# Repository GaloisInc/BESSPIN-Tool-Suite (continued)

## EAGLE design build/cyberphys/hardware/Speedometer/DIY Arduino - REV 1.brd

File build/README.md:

# Builds for FETT #

This directory should include the instructions and codes needed to build the OSs and the apps for the bug bounty.

Initially, the builds will be leveraging [Besspin Tool-Suite](https://gitlab-ext.galois.com/ssith/tool-suite).

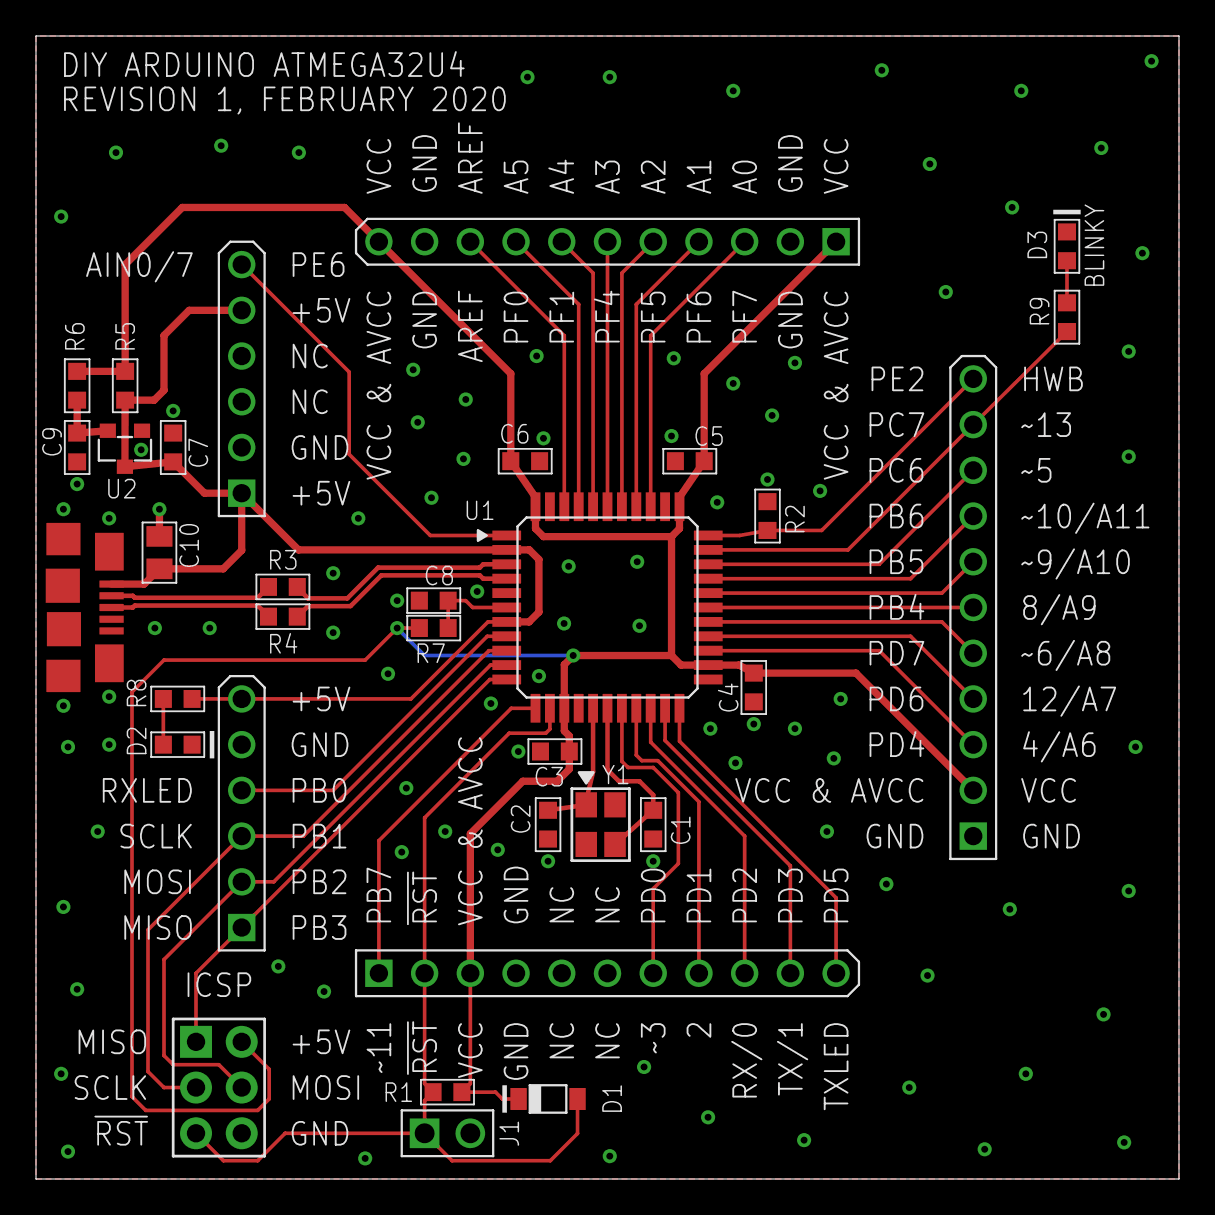
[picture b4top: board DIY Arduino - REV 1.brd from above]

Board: 2 copper layers, 63.5 x 63.5 mm, 33 parts (0 on the bottom side), 41 nets.

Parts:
C1, C2: 18p; EIA0603
C3, C4, C5, C6: 0.1u; EIA0603
C7, C8, C9: 1u; EIA0603
C10: 10u; EIA0805
CN1: 2X3M; 2X3_100MIL_ICSP
CN2: 10118192-0002LF; AMPHENOL_10118192-0002LF
CN3, CN4: 1X6_100MIL_THRU
CN5, CN6, CN7: 1X11_100MIL_THRU
D1: 1N4148WTR; SOD-123
D2: GREEN; EIA0603_LED
D3: RED; EIA0603_LED
J1: 1X2_100MIL_THRU
R1, R2: 10k; EIA0603
R3, R4: 22; EIA0603
R5: 0; EIA0603
R6, R7: DNS; EIA0603
R8, R9: 1k; EIA0603
U1: ATMEGA32U4-AUR; TQFP-44
U2: AP2125N-3.3; SOT23-3
Y1: 16 MHz; EPSON_FA-238

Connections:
!RST: CN1.5, CN5.2, D1.A, J1.1, R1.P$1, U1.13
+3V3: C9.P$2, R6.P$1, U2.2
AREF: CN7.9, U1.42
D_N: R3.P$2, U1.3
D_P: R4.P$2, U1.4
GND: C1.P$1, C2.P$1, C3.P$1, C4.P$1, C5.P$1, C6.P$1, C7.P$1, C8.P$1, C9.P$1, C10.P$1, CN1.6, CN2.5, CN2.TAB1, CN2.TAB2, CN2.TAB3, CN2.TAB4, CN2.TAB5, CN2.TAB6, CN3.2, CN4.5, CN5.4, CN5.5, CN5.6, CN6.1, CN7.2, CN7.10, D2.C, D3.C, J1.2, R2.P$1, U1.5, U1.15, U1.23, U1.35, U1.43, U2.1, Y1.2, Y1.4
unnamed: C2.P$2, U1.16, Y1.1
unnamed: D3.A, R9.P$1
unnamed: C8.P$2, R7.P$1, U1.6
unnamed: C1.P$2, U1.17, Y1.3
unnamed: D2.A, R8.P$1
PB0: CN4.4, U1.8
PB1: CN1.3, CN4.3, U1.9
PB2: CN1.4, CN4.2, U1.10
PB3: CN1.1, CN4.1, U1.11
PB4: CN6.6, U1.28
PB5: CN6.7, U1.29
PB6: CN6.8, U1.30
PB7: CN5.1, U1.12
PC6: CN6.9, U1.31
PC7: CN6.10, R9.P$2, U1.32
PD0: CN5.7, U1.18
PD1: CN5.8, U1.19
PD2: CN5.9, U1.20
PD3: CN5.10, U1.21
PD4: CN6.3, U1.25
PD5: CN5.11, U1.22
PD6: CN6.4, U1.26
PD7: CN6.5, U1.27
PE2: CN6.11, R2.P$2, U1.33
PE6: CN3.6, U1.1
PF0: CN7.8, U1.41
PF1: CN7.7, U1.40
PF4: CN7.6, U1.39
PF5: CN7.5, U1.38
PF6: CN7.4, U1.37
PF7: CN7.3, U1.36
USB_+5V: C7.P$2, C10.P$2, CN2.1, CN3.1, CN3.5, CN4.6, R5.P$2, R8.P$2, U1.2, U1.7, U2.3
USB_D_N: CN2.2, R3.P$1
USB_D_P: CN2.3, R4.P$1
VCC_&_AVCC: C3.P$2, C4.P$2, C5.P$2, C6.P$2, CN1.2, CN5.3, CN6.2, CN7.1, CN7.11, D1.C, R1.P$2, R5.P$1, R6.P$2, R7.P$2, U1.14, U1.24, U1.34, U1.44

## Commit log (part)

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2021-06-22 Fixed hack offsets and updated comments for clarity.
2021-06-22 change p[edal activity logic, update director whitelists
2021-06-22 Update config to use fixed binaries
2021-06-22 Fix chack generating script
2021-06-22 Bump submodule for latest binaries
2021-06-22 recover the vehicle connection if socket error occurs
2021-06-23 Working ECU hacks
2021-06-23 Ignition director fix
2021-06-23 Config updates
2021-06-23 add the checkAgainstValidScores option
2021-06-23 update the vulClassScore utility + documentation after adding checkAgainstValidScores
2021-06-23 Current changes
2021-06-23 fix can display issues
2021-06-24 remove unused file
2021-06-24 add a function call to avoid optimizing the integer overflow
2021-06-25 periodic update to the CI/AWS info
2021-06-25 there is no need to use the customized one, just use the regex printed by runTests
2021-06-25 bug in the new weightedAvgScore in case of errors
2021-06-25 new test 128 with add/mult variants -- constant values still
2021-06-25 Ok fine, I am not going to change all NE tests to be smart, let's stay like this
2021-06-26 Update regular and hacked infotainment server
2021-06-26 Update canlib, add DLC fields and component error IDs
2021-06-26 Can display - proper ident to show debug output
2021-06-26 Scenario tweaks
2021-06-26 Bump submnodules
2021-06-26 Fix the EOF exception
2021-06-26 Fix path typo
2021-06-28 fix the extra define in test_128
2021-06-30 systemd service files
2021-06-30 Requested fixes - mostly typos/formatting/comments
2021-06-30 start monitor first so that force feedback with happen with BeamNG
2021-06-30 not sure why the webcam js was commented out
2021-06-30 use 16:9 webcam settings
2021-07-01 Add a mode that leaks pointers instead of strings
    The new code stores a secret pointer surrounded by two pads pointers
    (NULL-derived capabilities on CHERI). The secret pointer is stored
    without the GLOBAL bit set (making it LOCAL) and when allocating results
    buffers, the STORE_LOCAL permission is stripped from the buffer. This
    causes a fault when attempting to retrieve the secret value.
    Enable this mode on SRI/Cambridge systems.
2021-07-05 changes to incorporate kaia videos
2021-07-06 add configurable brightness factor
2021-07-06 Fix struct packing
2021-07-06 fix backgrounds
2021-07-06 fix hack14 bg
2021-07-06 continue button for hack12
2021-07-07 fix test 761 -- free the bad pointer
2021-07-23 Better ident in commander.py
2021-07-23 Small tweaks in ignition for better user experience
2021-07-23 Clearly mark that CHERI is not supported to boot from flash
2021-07-23 Attempt to fix RTLINK File exists error when attemting to bring up eth0 on debian
2021-07-23 Add a small deploy script for cyberphys nodes
2021-07-23 Enable booting from flash for the debian targets. This is much faster and works quite well. Restarting the targets doesn't seem to work very well, hence the FreeRTOS targets are non-persistent That k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
2021-07-23 Bump submodules
2021-07-26 Save net setup script for the Admin PC
2021-07-26 Better document hacker kiosk backend
2021-07-26 Explain how to possibly improve the hacker experience with the infotainment hacks
2021-07-28 Update submodules
2021-07-28 Update submodules properly
2021-08-04 Fix test mode for kiosk
2021-08-04 Add debug info to the director
2021-08-05 Update startup tmux script to monitor components from the Adim PC
2021-08-05 Temporarily don't restart components, only targets
2021-08-05 Fix test mode of the kiosk
2021-08-05 Temporarily switch the kiosk back to test mode
2021-08-17 do not print every program vcu118 on freertos
2021-08-17 Config for easier testing of debian crashes
2021-08-17 send zmq reset command when new button is pressed on infotainment
2021-08-17 new state transitions diagram
2021-08-17 Add DebianPc
2021-08-17 Update kiosk transitions, and implement heartbeat response
2021-08-17 Update can-display backend, implement hearbeat response
2021-08-18 use pkill instead of the 5-pipes command
2021-08-18 load address misaligned in test 761 on FreeRTOS
2021-08-18 using sweet ATEM js package I found
2021-08-18 add state machine diagram generator for documentation of ignition director (#1253)
2021-08-18 added some notes to plan the new state machine diagram (#1253)
2021-08-19 should not use <runCommand> while TtyLogger is up and running -- this is a threading no no
2021-08-19 Better initialization, and better graph drawing
2021-08-19 Fix typo in state machine
2021-08-19 Unify CMD message handling across components
2021-08-19 Add configs for each system
2021-08-19 Better docs
2021-08-19 Use kill infotainment script only on debian
2021-08-19 Clean up CMD msg handling code
2021-08-19 Fix restarting components
2021-08-19 Add unit test for kiosk tester
2021-08-19 First pass of specs update
2021-08-20 Update infotainmetn specs
2021-08-20 Reset service on FreeBSD as well
2021-08-20 Update canspecs to contain funtionality level message
2021-08-20 Add automated scenario testing in a loop
2021-08-20 First shot of infotainment UI backend (for resetting BeamNg)
2021-08-20 Deploy to infotainment client as well
2021-08-20 Include component ID notes
2021-08-20 Make sure the OTA client is properly initialized at startup
2021-08-22 Change id -> cid so keywords are not clashing
2021-08-22 Kiosk backend bug fix (improper return)
2021-08-22 Increase default timeout in tests
2021-08-22 Fix bug in can msg parsing
2021-08-22 Simplify components
2021-08-23 Fix #1262 - disable infotainment sound in self-driving mode
2021-08-23 Update canspecs with error ids
2021-08-23 Stop periodically sending IGNITION_READY (nobody is listening)
2021-08-23 Comment cleanup in kiosk
2021-08-23 Stub out error logging on can-display
2021-08-23 stop audio mixer on sound enable / disable
2021-08-23 Fix player
2021-08-23 Fix debug prints
2021-08-23 reset button styling
2021-08-23 logging typo / copy paste error
2021-08-25 Update startup scripts
2021-08-25 Add custom target names and hostnames
2021-08-25 Update canlib with ComponentId<->ComponentName dictionary
2021-08-25 can display debug output
2021-08-25 parse error messages differently
2021-08-25 fix typo
2021-08-25 hide scrollbars
2021-08-25 update debug more often
2021-08-25 Simplify director
2021-08-25 Add Can display debug output (#1264)
2021-08-26 tabs->spaces to make linter happy
2021-08-26 Enable debug prints on Teensy
2021-08-26 Update tmux startup scripts
2021-08-26 Remove Z coordinate in GPS location
2021-08-26 Simplify ignition state machine
2021-08-26 better approach to managing atem connection
2021-08-26 add file logging to demonstrator
2021-08-27 Updated state machines
2021-08-27 Update canlib with more components
2021-08-27 Clean up ignition
2021-08-27 Notes about ignition state machine
2021-08-27 gate mac change to cyberphys mode only
2021-08-27 Correct analog inputs on teensy
2021-08-27 Add FUNCTIONALITY_LEVEL_NONE
2021-08-27 Add missing components and re-arrange
2021-08-27 Read teensy over serial
2021-08-30 Add try-catch around infotainment sound
2021-08-30 Fix typos in ignition
2021-08-30 button naming, atem improvements
2021-08-30 different method for calling atem script
2021-08-30 Small fixes
2021-08-30 add tcp timeout, component fix
2021-08-30 start monitor standalone for testing
2021-08-30 flesh out a simple heartbeat test
2021-08-30 start udp test for heartbeat monitor
2021-08-30 create heartbeat components
2021-08-30 add monitor submit recovery message
2021-08-30 start interfaces, ssh, http, and tcp monitors
2021-08-30 move prototype into ignition
2021-08-30 add ota health check
2021-08-30 run UDP health test
2021-08-30 add cc tcp bus to the main health monitor
2021-08-30 create ssh service monitors in main health monitor
2021-08-30 improve the ssh service description
2021-08-30 Round GPS coordinates
2021-08-30 repair health.py __init__, fix can repl args
2021-08-30 Update hacker kiosk to make it more robust, clarify the state machine
2021-08-31 localize health tests for better diagnostic information
2021-08-31 fix dict access
2021-08-31 add logger to health.py, create a readable health report property
2021-08-31 add health monitoring component to ignition director
2021-08-31 fix bad properties, rename the health monitor tool to monitor_health.py
2021-08-31 fix bad access in monitor, fix for director
2021-08-31 De-noise heartbeat responses
2021-08-31 Start of director cleanup
2021-08-31 Add more components
2021-08-31 Simplify ignition director
2021-08-31 Start with minimal functionality
2021-08-31 Added component IDs
2021-08-31 Add component comments
2021-08-31 use health monitor component with send restart requests, determine functionality level
2021-08-31 change health report key prefix
2021-08-31 don't show initial timer settings screen
2021-08-31 Small fixes in components
2021-08-31 switch to full functionality, commented heartbeat monitor in ignition for integration planning
2021-09-01 add send_msg to CAN interface
2021-09-01 add health report start in director
2021-09-01 update health monitor to use the can multiverse
2021-09-01 hide dev tools in production
2021-09-01 create Serial component
2021-09-01 Use Teensy in a simple thread
2021-09-01 Cleanup services and startup
2021-09-01 Add comments for the health check
2021-09-01 Check health only periodically
2021-09-01 print health report
2021-09-15 Minor fixes in deploy scripts
2021-09-15 Added teensy monitor
2021-09-15 Temporarily disable infotainment for remote testing without a sound endpoint
2021-09-15 Fix teensy
2021-09-15 Better serial port decoding, peroperly schedule health check
2021-09-15 fix health check counter
2021-09-15 Better health monitoring
2021-09-16 Remove comp_poller from the director
2021-09-16 Director updates
2021-09-17 Teensy health check, easter egg race car
2021-09-17 Add missing scripts
2021-09-20 Remove non-source code files, they are moved into https://github.com/GaloisInc/BESSPIN-Demonstrator
2021-09-21 Remove non-source code files (#1273)
    they are moved into https://github.com/GaloisInc/BESSPIN-Demonstrator
2021-09-21 Add back scripts, removed by accident
2021-09-21 Test health monitor without TCP elements
2021-09-21 Try to simplify the monitor
2021-09-21 Start reimplementing health monitor
2021-09-21 Add systemctl service health monitor query
2021-09-21 Add ping monitors
2021-09-21 Attempt for UDP monitor
2021-09-21 Simplify udp health monitor
2021-09-21 Maybe tcp monitor works better
2021-09-21 Cleanup monitor
2021-09-22 Run component health check
2021-09-22 make sure atem control script exits properly
2021-09-22 formatting
2021-09-22 Better print from health check
2021-09-22 Fix zombie atem process (#1275)
2021-09-22 Debug outputs, change health monitor frequency
2021-09-22 Introduce functionality levels
2021-09-22 Add functionality level switch
2021-09-22 Fix system status handling
2021-09-23 Update functionality levels
2021-09-23 Func level cleanup
2021-09-23 Fine tune the system health monitoring machine
2021-09-23 Repeatedly report errors
2021-09-23 Logic fix in CAN display
2021-09-23 Update hacker kiosk from Pi to NUC, remove old health monitor
2021-09-27 Check if simulator connection is OK, add cmd line arg to disable sound when starting the ignition
2021-09-27 Fix typos
2021-09-27 Small tweaks
2021-09-27 Health monitor refactor (#1274)
    Fixes health monitor, various minor fixes for the demo
2022-06-22 Bump numpy from 1.19.2 to 1.22.0 in /besspin/cyberPhys/cyberphyslib
    Bumps [numpy](https://github.com/numpy/numpy) from 1.19.2 to 1.22.0.
    - [Release notes](https://github.com/numpy/numpy/releases)
    - [Changelog](https://github.com/numpy/numpy/blob/main/doc/HOWTO_RELEASE.rst)
    - [Commits](https://github.com/numpy/numpy/compare/v1.19.2...v1.22.0)
    ---
    updated-dependencies:
2022-09-13 Add mouse-config script
2022-09-16 Hacker Kiosk museum updates
2022-09-16 Bump cyberphyslib version to better recognize properly updated deployment
2022-09-16 Infotainment server museum edition (hacked and regular server in one, switches where it receives button presses from based on the state of the simulator - scenario & hack active)
2022-09-16 Modded deploy script, uncomment as needed
2022-09-16 Updated startup script for the museum (main change: no adminPc/no FPGAs)
2022-09-16 Don't change color for the infotainment hack
